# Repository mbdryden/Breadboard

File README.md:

# Breadboard
This repository contains the breadboard-level hardware, firmware, and supporting documentation for the Senior Design project. It is used for early prototyping, testing, and validation of system functionality prior to PCB implementation.

see the site here: https://mbdryden.github.io/Breadboard/

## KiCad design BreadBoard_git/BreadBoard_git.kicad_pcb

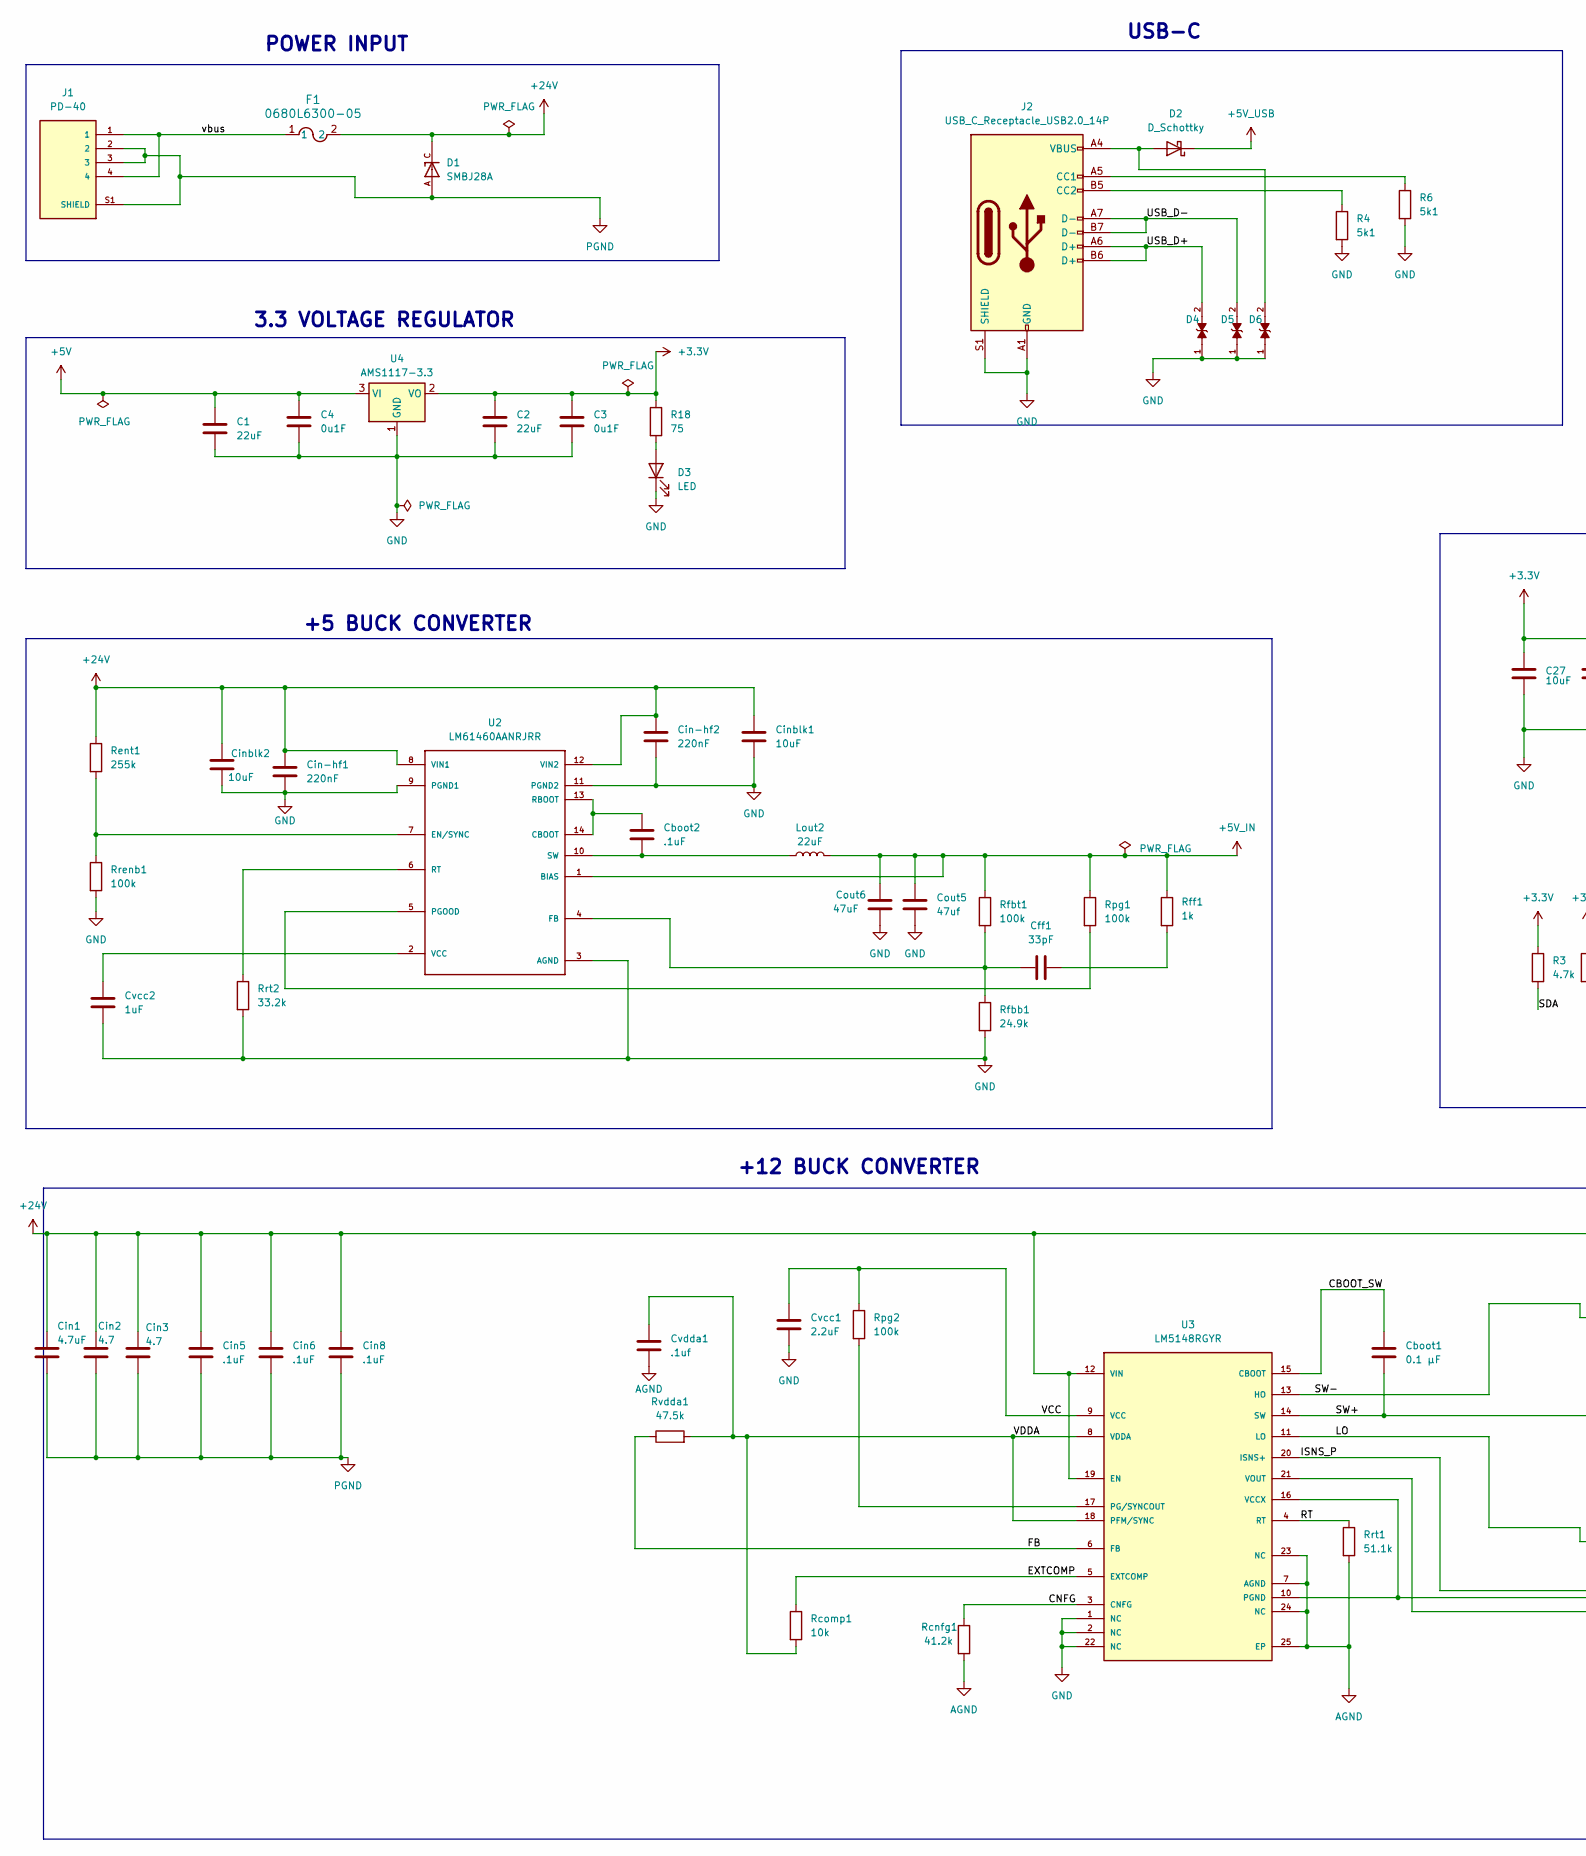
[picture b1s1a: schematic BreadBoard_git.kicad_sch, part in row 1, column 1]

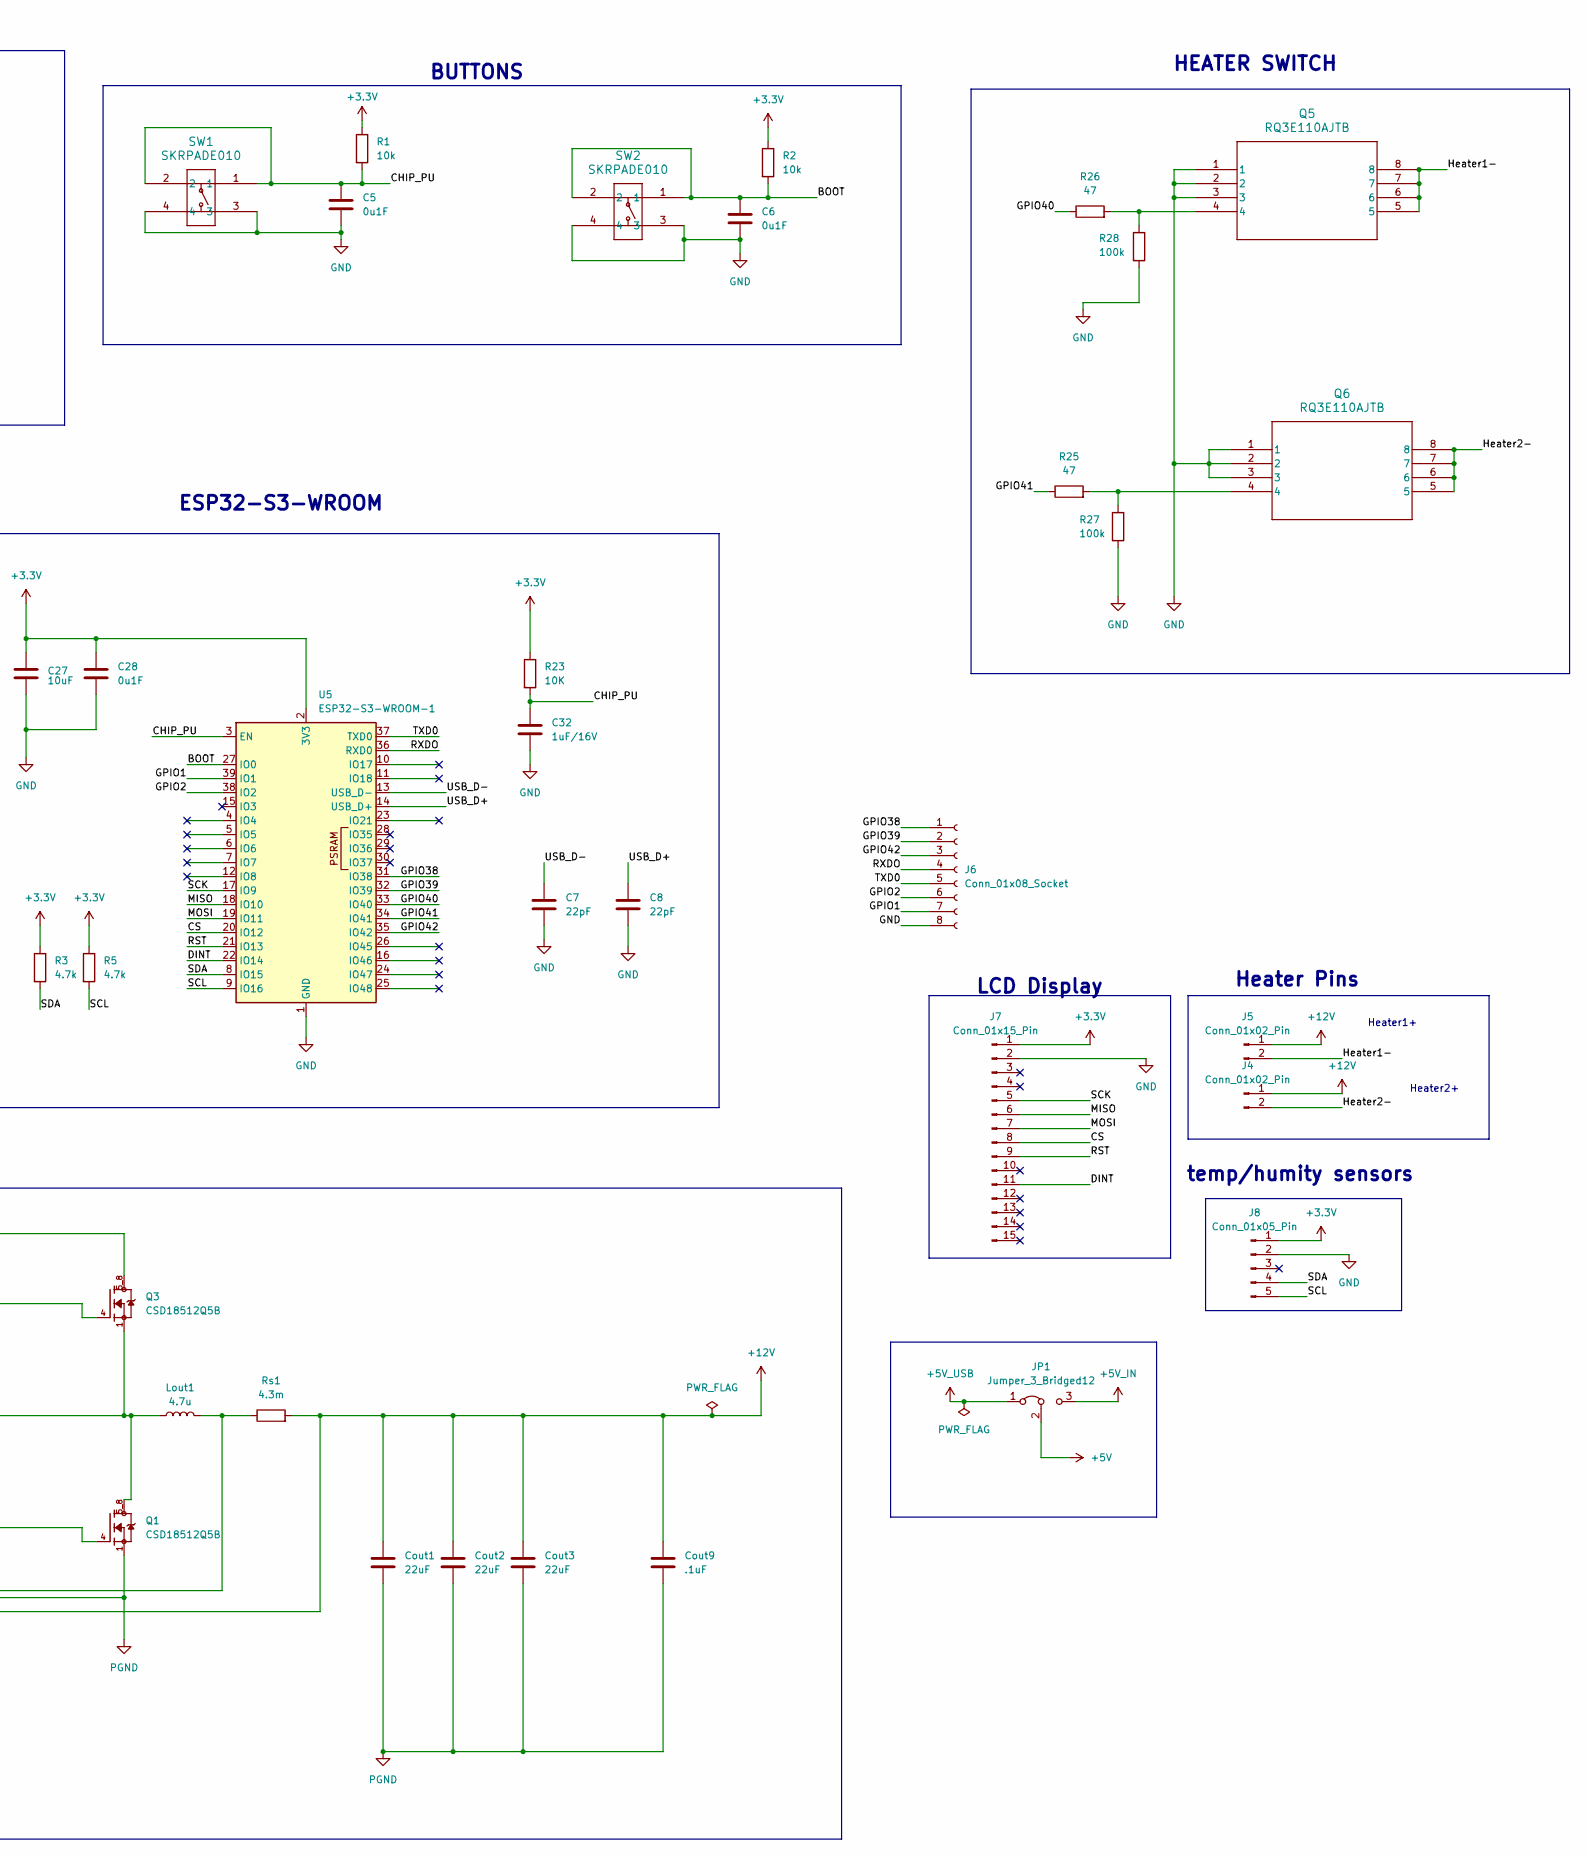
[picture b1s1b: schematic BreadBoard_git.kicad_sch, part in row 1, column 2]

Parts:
C1, C2: 22uF; C_0603_1608Metric_Pad1.08x0.95mm_HandSolder
C3, C4, C5, C6, C28: 0u1F; C_0603_1608Metric_Pad1.08x0.95mm_HandSolder
C7, C8: 22pF; C_0402_1005Metric_Pad0.74x0.62mm_HandSolder
C27: 10uF; C_0805_2012Metric_Pad1.18x1.45mm_HandSolder
C32: 1uF/16V; C_0603_1608Metric_Pad1.08x0.95mm_HandSolder
Cboot1: 0.1 µF; R_0402_1005Metric_Pad0.72x0.64mm_HandSolder
Cboot2: .1uF; C_0201_0603Metric_Pad0.64x0.40mm_HandSolder
Cff1: 33pF; C_0201_0603Metric_Pad0.64x0.40mm_HandSolder
Cin1: 4.7uF; C_1210_3225Metric_Pad1.33x2.70mm_HandSolder
Cin2, Cin3: 4.7; C_1210_3225Metric_Pad1.33x2.70mm_HandSolder
Cin5, Cin6, Cin8: .1uF; C_0402_1005Metric_Pad0.74x0.62mm_HandSolder
Cin-hf1, Cin-hf2: 220nF; C_0603_1608Metric_Pad1.08x0.95mm_HandSolder
Cinblk1, Cinblk2: 10uF; C_1210_3225Metric_Pad1.33x2.70mm_HandSolder
Cout1, Cout2, Cout3: 22uF; C_1210_3225Metric_Pad1.33x2.70mm_HandSolder
Cout5: 47uf; C_1210_3225Metric_Pad1.33x2.70mm_HandSolder
Cout6: 47uF; C_1210_3225Metric_Pad1.33x2.70mm_HandSolder
Cout9: .1uF; C_0402_1005Metric_Pad0.74x0.62mm_HandSolder
Cvcc1: 2.2uF; C_0402_1005Metric_Pad0.74x0.62mm_HandSolder
Cvcc2: 1uF; C_0603_1608Metric_Pad1.08x0.95mm_HandSolder
Cvdda1: .1uf; C_0402_1005Metric_Pad0.74x0.62mm_HandSolder
D1: SMBJ28A; DIOM5436X244N; PARTREV 30-Jun-2021
D2: D_Schottky; D_0603_1608Metric_Pad1.05x0.95mm_HandSolder
D3: LED; LED_0201_0603Metric
D4, D5, D6: LESD5D5.0CT1G; TVS_LESD5D5.0CT1G; PARTREV O
F1: 0680L6300-05; FUS_CB_3216TD
J1: PD-40; CUI_PD-40; PARTREV 02/18/2022
J2: USB_C_Receptacle_USB2.0_14P; USB_C_Receptacle_HRO_TYPE-C-31-M-12
J4, J5: Conn_01x02_Pin; PinHeader_1x02_P2.54mm_Vertical
J6: Conn_01x08_Socket; PinSocket_1x08_P2.54mm_Vertical
J7: Conn_01x15_Pin; PinSocket_1x15_P1.00mm_Vertical
J8: Conn_01x05_Pin; PinSocket_1x05_P1.00mm_Vertical
JP1: Jumper_3_Bridged12; PinHeader_1x03_P2.54mm_Vertical
Lout1: 4.7u; WSR-L
Lout2: 22uF; WSR-L
Q1, Q3: CSD18512Q5B; TRANS_CSD18512Q5B; PARTREV A
Q5, Q6: RQ3E110AJTB; HSMT8_ROM-L
R1, R2: 10k; R_0603_1608Metric_Pad0.98x0.95mm_HandSolder
R3, R5: 4.7k
R4, R6: 5k1; R_0201_0603Metric_Pad0.64x0.40mm_HandSolder
R18: 75; R_0603_1608Metric_Pad0.98x0.95mm_HandSolder
R23: 10K; R_0603_1608Metric_Pad0.98x0.95mm_HandSolder
R25, R26: 47; R_0603_1608Metric_Pad0.98x0.95mm_HandSolder
R27, R28: 100k; R_0603_1608Metric_Pad0.98x0.95mm_HandSolder
Rcnfg1: 41.2k; R_0402_1005Metric_Pad0.72x0.64mm_HandSolder
Rcomp1: 10k; R_0201_0603Metric_Pad0.64x0.40mm_HandSolder
Rent1: 255k; R_0603_1608Metric_Pad0.98x0.95mm_HandSolder
Rfbb1: 24.9k; R_0603_1608Metric_Pad0.98x0.95mm_HandSolder
Rfbt1: 100k; R_0603_1608Metric_Pad0.98x0.95mm_HandSolder
Rff1: 1k; R_0603_1608Metric_Pad0.98x0.95mm_HandSolder
Rpg1: 100k; R_0603_1608Metric_Pad0.98x0.95mm_HandSolder
Rpg2: 100k; R_0201_0603Metric_Pad0.64x0.40mm_HandSolder
Rrenb1: 100k; R_0603_1608Metric_Pad0.98x0.95mm_HandSolder
Rrt1: 51.1k; R_0402_1005Metric_Pad0.72x0.64mm_HandSolder
Rrt2: 33.2k; R_0603_1608Metric_Pad0.98x0.95mm_HandSolder
Rs1: 4.3m; R_0508_1220Metric_Pad1.12x2.15mm_HandSolder
Rvdda1: 47.5k; R_0201_0603Metric_Pad0.64x0.40mm_HandSolder
SW1, SW2: SKRPADE010; SKRPADE010_AAL
U2: LM61460AANRJRR; IC_LM61460AANRJRR; PARTREV A
U3: LM5148RGYR; QFN50P550X350X100-25N; PARTEV February 2023
U4: AMS1117-3.3; SOT-223-3_TabPin2
U5: ESP32-S3-WROOM-1

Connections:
+3.3V: C2.2, C3.1, C27.1, C28.1, J7.1, J8.1, R1.1, R2.1, R3.1, R5.1, R18.1, R23.1, U4.2 (VO), U5.2 (3V3)
+5V: C1.1, C4.1, JP1.2 (C), U4.3 (VI)
+5V_IN: Cout5.1, Cout6.1, JP1.3 (B), Lout2.2, Rfbt1.1, Rff1.1, Rpg1.1, U2.1 (BIAS)
+5V_USB: D2.1 (K), JP1.1 (A)
+12V: Cout1.1, Cout2.1, Cout3.1, Cout9.1, J4.1, J5.1, Rs1.2, U3.21 (VOUT)
+24V: Cin1.1, Cin2.1, Cin3.1, Cin5.1, Cin6.1, Cin8.1, Cin-hf1.1, Cin-hf2.1, Cinblk1.1, Cinblk2.1, D1.C, F1.2, Q3.5_8, Rent1.1, U2.8 (VIN1), U2.12 (VIN2), U3.12 (VIN), U3.19 (EN)
/BOOT: C6.1, R2.2, SW2.1, SW2.2, U5.27 (IO0)
/CBOOT_SW: Cboot1.1, U3.15 (CBOOT)
/CHIP_PU: C5.1, C32.1, R1.2, R23.2, SW1.1, SW1.2, U5.3 (EN)
/CNFG: Rcnfg1.1, U3.3 (CNFG)
/CS: J7.8, U5.20 (IO12)
/DINT: J7.11, U5.22 (IO14)
/EXTCOMP: Rcomp1.1, U3.5 (EXTCOMP)
/FB: Rvdda1.1, U3.6 (FB)
/GPIO1: J6.7, U5.39 (IO1)
/GPIO2: J6.6, U5.38 (IO2)
/GPIO38: J6.1, U5.31 (IO38)
/GPIO39: J6.2, U5.32 (IO39)
/GPIO40: R26.1, U5.33 (IO40)
/GPIO41: R25.1, U5.34 (IO41)
/GPIO42: J6.3, U5.35 (IO42)
/Heater1-: J5.2, Q5.5, Q5.6, Q5.7, Q5.8
/Heater2-: J4.2, Q6.5, Q6.6, Q6.7, Q6.8
/ISNS_P: Lout1.2, Rs1.1, U3.20 (ISNS+)
/LO: Q1.4, U3.11 (LO)
/MISO: J7.6, U5.18 (IO10)
/MOSI: J7.7, U5.19 (IO11)
/RST: J7.9, U5.21 (IO13)
/RT: Rrt1.1, U3.4 (RT)
/RXDO: J6.4, U5.36 (RXD0)
/SCK: J7.5, U5.17 (IO9)
/SCL: J8.5, R5.2, U5.9 (IO16)
/SDA: J8.4, R3.2, U5.8 (IO15)
/SW+: Cboot1.2, Lout1.1, Q1.5_8, Q3.1, Q3.2, Q3.3, U3.14 (SW)
/SW-: Q3.4, U3.13 (HO)
/TXD0: J6.5, U5.37 (TXD0)
/USB_D+: C8.1, D4.2, J2.A6 (D+), J2.B6 (D+), U5.14 (USB_D+)
/USB_D-: C7.1, D5.2, J2.A7 (D-), J2.B7 (D-), U5.13 (USB_D-)
/VCC: Cvcc1.1, Rpg2.1, U3.9 (VCC)
/VDDA: Cvdda1.1, Rcomp1.2, Rvdda1.2, U3.8 (VDDA), U3.18 (PFM/SYNC)
/vbus: F1.1, J1.1, J1.4
AGND: Cvdda1.2, Rcnfg1.2, Rrt1.2, U3.7 (AGND), U3.23 (NC), U3.24 (NC), U3.25 (EP)
GND: C1.2, C2.1, C3.2, C4.2, C5.2, C6.2, C7.2, C8.2, C27.2, C28.2, C32.2, Cin-hf1.2, Cin-hf2.2, Cinblk1.2, Cinblk2.2, Cout5.2, Cout6.2, Cvcc1.2, Cvcc2.2, D3.1 (K), D4.1, D5.1, D6.1, J2.A1 (GND), J2.A12 (GND), J2.B1 (GND), J2.B12 (GND), J2.S1 (SHIELD), J6.8, J7.2, J8.2, Q5.1, Q5.2, Q5.3, Q6.1, Q6.2, Q6.3, R4.2, R6.2, R27.1, R28.1, Rfbb1.2, Rrenb1.2, Rrt2.2, SW1.3, SW1.4, SW2.3, SW2.4, U2.3 (AGND), U2.9 (PGND1), U2.11 (PGND2), U3.1 (NC), U3.2 (NC), U3.22 (NC), U4.1 (GND), U5.1 (GND), U5.40 (GND), U5.41 (GND)
unnamed: Cff1.2, Rff1.2
unnamed: D2.2 (A), D6.2, J2.A4 (VBUS), J2.A9 (VBUS), J2.B4 (VBUS), J2.B9 (VBUS)
unnamed: D3.2 (A), R18.2
unnamed: J2.A5 (CC1), R6.1
unnamed: J2.B5 (CC2), R4.1
unnamed: Q5.4, R26.2, R28.2
unnamed: Q6.4, R25.2, R27.2
unnamed: Cboot2.1, U2.13 (RBOOT), U2.14 (CBOOT)
unnamed: Rent1.2, Rrenb1.1, U2.7 (EN/SYNC)
unnamed: Cff1.1, Rfbb1.1, Rfbt1.2, U2.4 (FB)
unnamed: Rpg1.2, U2.5 (PGOOD)
unnamed: Rrt2.1, U2.6 (RT)
unnamed: Cboot2.2, Lout2.1, U2.10 (SW)
unnamed: Cvcc2.1, U2.2 (VCC)
unnamed: Rpg2.2, U3.17 (PG/SYNCOUT)
PGND: Cin1.2, Cin2.2, Cin3.2, Cin5.2, Cin6.2, Cin8.2, Cout1.2, Cout2.2, Cout3.2, Cout9.2, D1.A, J1.2, J1.3, J1.S1 (SHIELD), Q1.1, Q1.2, Q1.3, U3.10 (PGND), U3.16 (VCCX)

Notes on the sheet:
ESP32-S3-WROOM
LCD Display
Heater Pins
Heater1+
temp/humity sensors
3.3 VOLTAGE REGULATOR
POWER INPUT
USB-C
+12 BUCK CONVERTER
Heater2+
BUTTONS
+5 BUCK CONVERTER
HEATER SWITCH

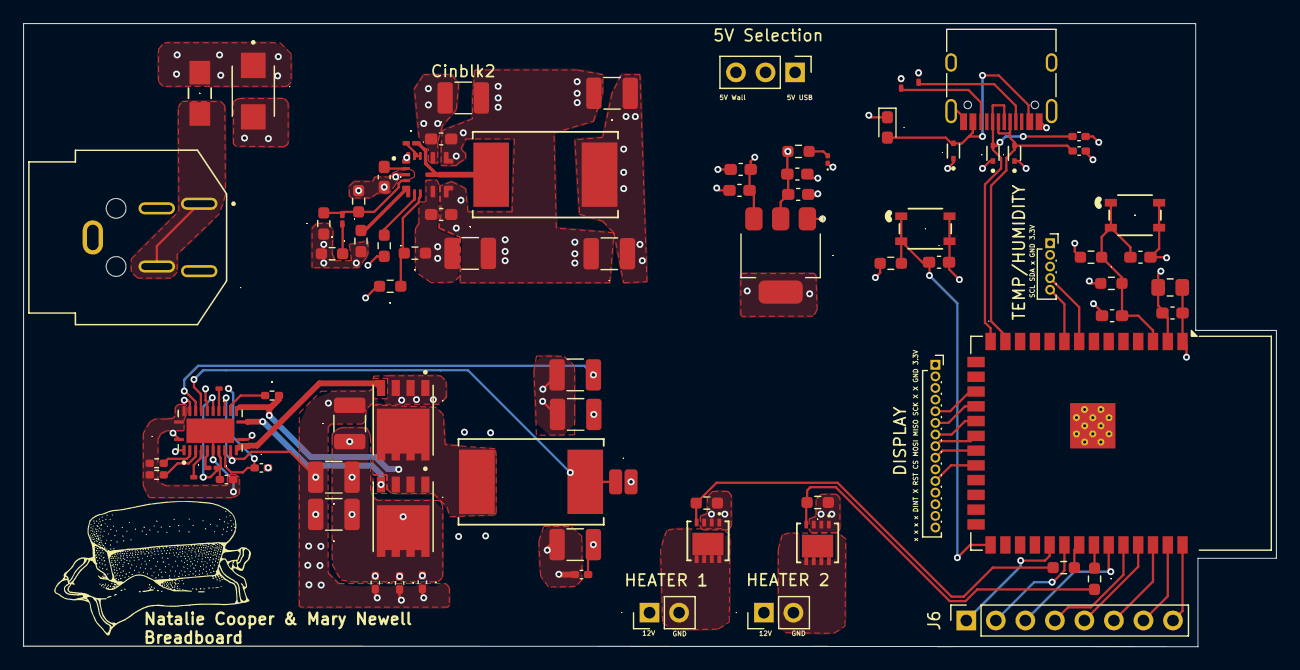
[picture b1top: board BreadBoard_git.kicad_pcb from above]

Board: 4 copper layers, 107.8 x 53.6 mm, 83 parts (0 on the bottom side), 59 nets.

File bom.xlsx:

Id;"Designator";"Footprint";"Quantity";"Designation";"Supplier and ref";
1;"Cinblk1 | Cinblk2";"C_1210_3225Metric_Pad1.33x2.70mm_HandSolder";2;"10uF";;;
2;"Q3 | Q1";"TRANS_CSD18512Q5B";2;"CSD18512Q5B";;;
3;"Cout6";"C_1210_3225Metric_Pad1.33x2.70mm_HandSolder";1;"47uF";;;
4;"Cvdda1";"C_0402_1005Metric_Pad0.74x0.62mm_HandSolder";1;".1uf";;;
5;"R4 | R6";"R_0201_0603Metric_Pad0.64x0.40mm_HandSolder";2;"5k1";;;
6;"Cout3 | Cout1 | Cout2";"C_1210_3225Metric_Pad1.33x2.70mm_HandSolder";3;"22uF";;;
7;"F1";"FUS_CB_3216TD";1;"0680L6300-05";;;
8;"Cin-hf2 | Cin-hf1";"C_0603_1608Metric_Pad1.08x0.95mm_HandSolder";2;"220nF";;;
9;"J6";"PinSocket_1x08_P2.54mm_Vertical";1;"Conn_01x08_Socket";;;
10;"C28 | C3 | C4 | C5 | C6";"C_0603_1608Metric_Pad1.08x0.95mm_HandSolder";5;"0u1F";;;
11;"J1";"CUI_PD-40";1;"PD-40";;;
12;"J8";"PinSocket_1x05_P1.00mm_Vertical";1;"Conn_01x05_Pin";;;
13;"Rpg1 | Rfbt1 | R28 | R27 | Rrenb1";"R_0603_1608Metric_Pad0.98x0.95mm_HandSolder";5;"100k";;;
14;"R26 | R25";"R_0603_1608Metric_Pad0.98x0.95mm_HandSolder";2;"47";;;
15;"Cin2 | Cin3";"C_1210_3225Metric_Pad1.33x2.70mm_HandSolder";2;"4.7";;;
16;"Cout9 | Cin6 | Cin8 | Cin5";"C_0402_1005Metric_Pad0.74x0.62mm_HandSolder";4;".1uF";;;
17;"D4 | D6 | D5";"TVS_LESD5D5.0CT1G";3;"LESD5D5.0CT1G";;;
18;"Rcomp1";"R_0201_0603Metric_Pad0.64x0.40mm_HandSolder";1;"10k";;;
19;"J2";"USB_C_Receptacle_HRO_TYPE-C-31-M-12";1;"USB_C_Receptacle_USB2.0_14P";;;
20;"Rrt2";"R_0603_1608Metric_Pad0.98x0.95mm_HandSolder";1;"33.2k";;;
21;"Rent1";"R_0603_1608Metric_Pad0.98x0.95mm_HandSolder";1;"255k";;;
22;"R18";"R_0603_1608Metric_Pad0.98x0.95mm_HandSolder";1;"75";;;
23;"Lout1";"WSR-L";1;"4.7u";;;
24;"Q5 | Q6";"HSMT8_ROM-L";2;"RQ3E110AJTB";;;
25;"C7 | C8";"C_0402_1005Metric_Pad0.74x0.62mm_HandSolder";2;"22pF";;;
26;"Rs1";"R_0508_1220Metric_Pad1.12x2.15mm_HandSolder";1;"4.3m";;;
27;"R1 | R2";"R_0603_1608Metric_Pad0.98x0.95mm_HandSolder";2;"10k";;;
28;"U4";"SOT-223-3_TabPin2";1;"AMS1117-3.3";;;
29;"D1";"DIOM5436X244N";1;"SMBJ28A";;;
30;"J5 | J4";"PinHeader_1x02_P2.54mm_Vertical";2;"Conn_01x02_Pin";;;
31;"Rvdda1";"R_0201_0603Metric_Pad0.64x0.40mm_HandSolder";1;"47.5k";;;
32;"Cff1";"C_0201_0603Metric_Pad0.64x0.40mm_HandSolder";1;"33pF";;;
33;"D3";"LED_0201_0603Metric";1;"LED";;;
34;"Cboot1";"R_0402_1005Metric_Pad0.72x0.64mm_HandSolder";1;"0.1 ¬µF";;;
35;"Cboot2";"C_0201_0603Metric_Pad0.64x0.40mm_HandSolder";1;".1uF";;;
36;"Rrt1";"R_0402_1005Metric_Pad0.72x0.64mm_HandSolder";1;"51.1k";;;
37;"Rpg2";"R_0201_0603Metric_Pad0.64x0.40mm_HandSolder";1;"100k";;;
38;"Cin1";"C_1210_3225Metric_Pad1.33x2.70mm_HandSolder";1;"4.7uF";;;
39;"C1 | C2";"C_0603_1608Metric_Pad1.08x0.95mm_HandSolder";2;"10uF";;;
40;"J7";"PinSocket_1x15_P1.00mm_Vertical";1;"Conn_01x15_Pin";;;
41;"U2";"IC_LM61460AANRJRR";1;"LM61460AANRJRR";;;
42;"SW1 | SW2";"SKRPADE010_AAL";2;"SKRPADE010";;;
43;"Cvcc2";"C_0603_1608Metric_Pad1.08x0.95mm_HandSolder";1;"1uF";;;
44;"Cvcc1";"C_0402_1005Metric_Pad0.74x0.62mm_HandSolder";1;"2.2uF";;;
45;"Rfbb1";"R_0603_1608Metric_Pad0.98x0.95mm_HandSolder";1;"24.9k";;;
46;"Rff1";"R_0603_1608Metric_Pad0.98x0.95mm_HandSolder";1;"1k";;;
47;"Lout2";"WSR-L";1;"22uF";;;
48;"C32";"C_0603_1608Metric_Pad1.08x0.95mm_HandSolder";1;"1uF/16V";;;
49;"D2";"D_0603_1608Metric_Pad1.05x0.95mm_HandSolder";1;"D_Schottky";;;
50;"Cout5";"C_1210_3225Metric_Pad1.33x2.70mm_HandSolder";1;"47uf";;;
51;"U5";"ESP32-S3-WROOM-1";1;"ESP32-S3-WROOM-1";;;
52;"U3";"QFN50P550X350X100-25N";1;"LM5148RGYR";;;
53;"R23";"R_0603_1608Metric_Pad0.98x0.95mm_HandSolder";1;"10K";;;
54;"C27";"C_0805_2012Metric_Pad1.18x1.45mm_HandSolder";1;"10uF";;;
55;"Rcnfg1";"R_0402_1005Metric_Pad0.72x0.64mm_HandSolder";1;"41.2k";;;

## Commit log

2026-01-30 Create git ignore
    ignore kicad files added
2026-01-30 edits on kicad
2026-02-03 work on lcd driver
2026-02-06 setting stuff up
2026-02-06 Move index.html to root for GitHub Pages
2026-02-06 main
2026-02-06 index
2026-02-18 login/signup working
2026-02-18 name page ugly but working
2026-02-18 different dashboards depending on cycle
2026-02-20 testing datetime
2026-02-20 Add flavor text to textfile
2026-02-20 made some pretty changes
2026-02-20 fixing favicon
2026-02-20 troubleshooting
2026-02-21 cutesy changes
2026-02-24 kicad
2026-02-25 temp page working and time left in cycle displayed on dash
2026-02-27 lcd driver
2026-03-04 temp and humidity display
2026-03-04 edited database to have boxes and users tables. header only shows on dashboard, not login/signup. box switching page added
2026-03-05 for communication subsystem
2026-03-06 changed page setup to decrease lag
2026-03-10 updated schmatic
2026-03-10 update with every resistor value
    updated schmatic
2026-03-10 add footprint cout
2026-03-10 updte
2026-03-10 update
    update
2026-03-10 potential poverwrite
2026-03-11 footprints not working
2026-03-11 brruuuuuhhhhhh
2026-03-11 small updates
2026-03-12 added navbar
2026-03-12 5V needs to be added
2026-03-13 most footprints in
2026-03-13 fix small bug with name subheader
2026-03-13 added different cycle times based on ratio and temp
2026-03-17 kicad library created
2026-03-18 libary update 75% footprints added
2026-03-18 layout!
2026-03-25 update!
2026-03-26 pcb updates
2026-03-27 updates!
2026-04-03 fixed cycle countdown
2026-04-15 Update sensorReadings.py
    Function to collect temperature and humidity values from the SHT45 sensor. *Converts values to Fahrenheit*
2026-04-15 Update code.py
    Treating file as my main function: has the while loop to call the control logic function at the determined 40 second time interval.
2026-04-15 Update controls_logic.py
    Controls logic code, calls the sensor readings function in here and does PID calculations and sets the PWM duty cycle based on that.
2026-04-21 test file
    create a file to test whole system prior to pcb
2026-04-27 Added pwm for second heater and capped highest duty to 80%
2026-04-27 Added integration with firebase user temperature range collection. Need to test and check!
2026-04-27 Added print statements for spec verification
2026-04-27 changed pwm cap
2026-04-28 add 2 min test cycle
2026-04-28 trying again
2026-04-28 fixed temperature validation
2026-04-30 fixed humidity
2026-04-30 added results page
2026-05-01 two minute test cycle
2026-05-01 fixing null temp error
2026-05-01 timing fix?
2026-05-01 quick temp fix
2026-05-01 higher temp
2026-05-01 fix bug
